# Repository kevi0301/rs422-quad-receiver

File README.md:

# RS-422 Quad Receiver PCB

4-channel RS-422 receiver PCB designed in KiCad with AC termination, TVS protection, test points, and fabrication outputs. 
## Features
- 4-channel RS-422 differential receiver
- AM26C32 receiver IC
- SM712 TVS protection for each input channel
- Configurable enable control with pull-up and pull-down resistors
- Power indicator with LED and 5V power input
- Local 0.1 uF decoupling capacitor
- Test points included in 5V, GND, and Y1-Y4 outputs
- 2-layer PCB with ground copper plane
- Mounting holes with copper keep-out areas
## PCB Design
- Designed and routed in KiCad
- Top and bottom copper routing
- Ground plane implemented on B.Cu
- DRC completed with 0 violations and 0 unrouted connections
- Silkscreen labeling added for debugging and board identification
## Fabrication
Gerber and Excellon PTH/NPTH drill files are included in the Fabrication folder.
## Project Status
PCB design and fabrication files complete. Physical fabrication and hardware validation have not yet been performed.

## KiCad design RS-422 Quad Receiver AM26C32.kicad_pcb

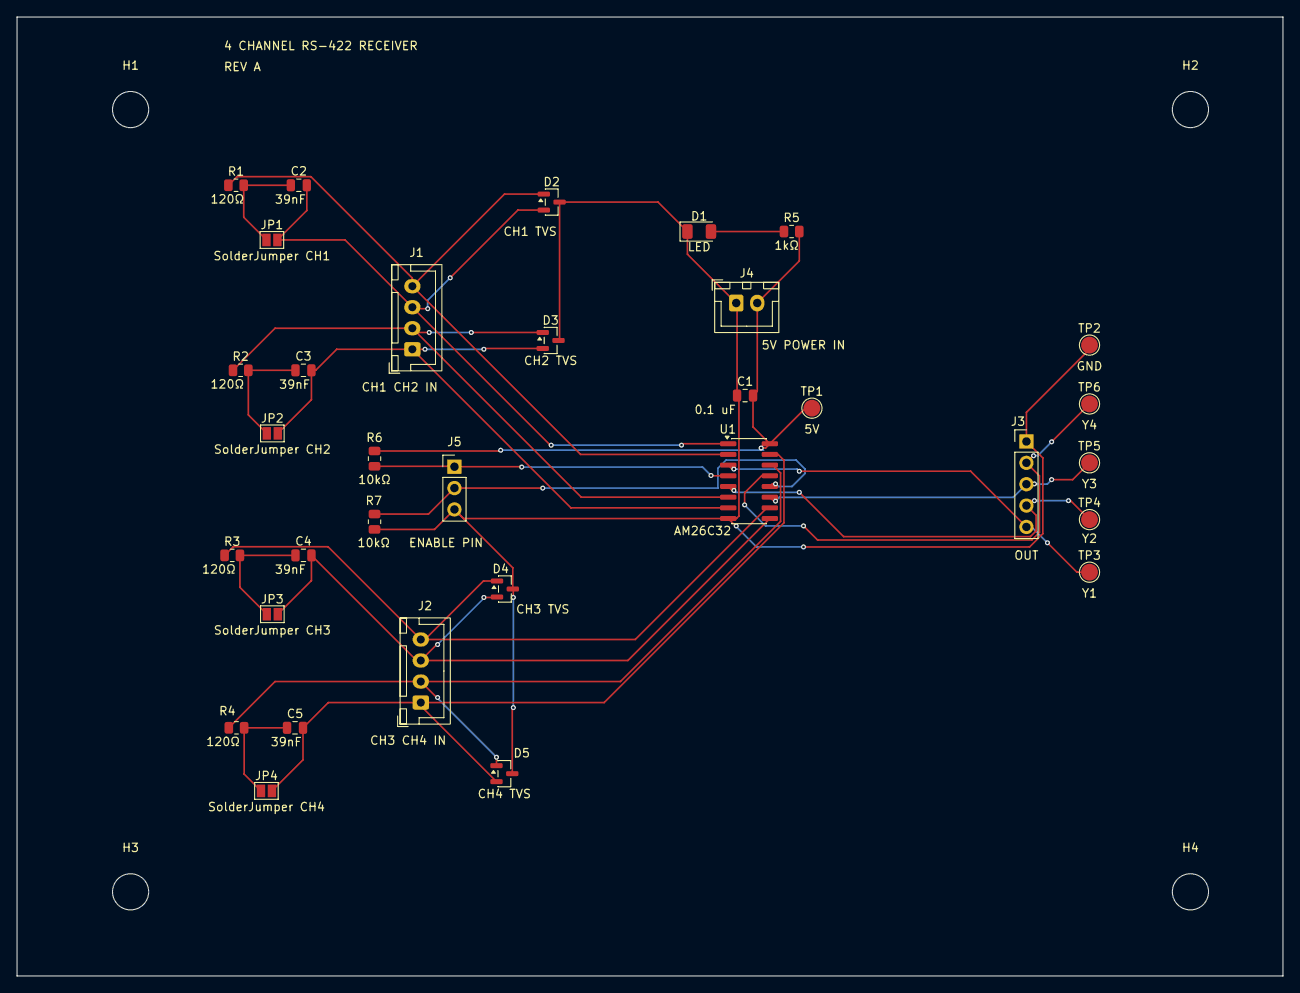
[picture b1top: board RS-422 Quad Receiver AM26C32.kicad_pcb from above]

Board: 2 copper layers, 150.5 x 114.0 mm, 37 parts (0 on the bottom side), 21 nets.

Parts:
C1: 0.1 uF; C_0805_2012Metric
C2, C3, C4, C5: 39nF; C_0805_2012Metric
D1: LED; LED_1206_3216Metric
D2: CH1 TVS; SOT-23
D3: CH2 TVS; SOT-23
D4: CH3 TVS; SOT-23
D5: CH4 TVS; SOT-23
H1, H2, H3, H4: MountingHole; MountingHole_4.3mm_M4
J1: CH1 CH2 IN; JST_XH_B4B-XH-A_1x04_P2.50mm_Vertical
J2: CH3 CH4 IN; JST_XH_B4B-XH-A_1x04_P2.50mm_Vertical
J3: OUT; PinHeader_1x05_P2.54mm_Vertical
J4: 5V POWER IN; JST_XH_B2B-XH-A_1x02_P2.50mm_Vertical
J5: ENABLE PIN; PinHeader_1x03_P2.54mm_Vertical
JP1: SolderJumper CH1; SolderJumper-2_P1.3mm_Open_Pad1.0x1.5mm
JP2: SolderJumper CH2; SolderJumper-2_P1.3mm_Open_Pad1.0x1.5mm
JP3: SolderJumper CH3; SolderJumper-2_P1.3mm_Open_Pad1.0x1.5mm
JP4: SolderJumper CH4; SolderJumper-2_P1.3mm_Open_Pad1.0x1.5mm
R1, R2, R3, R4: 120Ω; R_0805_2012Metric
R5: 1kΩ; R_0805_2012Metric
R6, R7: 10kΩ; R_0805_2012Metric
TP1: 5V; TestPoint_Pad_D2.0mm
TP2: GND; TestPoint_Pad_D2.0mm
TP3: Y1; TestPoint_Pad_D2.0mm
TP4: Y2; TestPoint_Pad_D2.0mm
TP5: Y3; TestPoint_Pad_D2.0mm
TP6: Y4; TestPoint_Pad_D2.0mm
U1: AM26C32; SOIC-16_3.9x9.9mm_P1.27mm

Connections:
+5V: C1.2, J4.2, R5.2, R6.1, TP1.1 (1_1), U1.16 (VDD)
/1A: D2.1 (A1), J1.4, R1.1, U1.2 (1A)
/1B: C2.2, D2.2 (A2), J1.3, JP1.2 (B), U1.1 (1B)
/2A: D3.1 (A1), J1.2, R2.1, U1.6 (2A)
/2B: C3.2, D3.2 (A2), J1.1, JP2.2 (B), U1.7 (2B)
/3A: D4.1 (A1), J2.4, R3.1, U1.10 (3A)
/3B: C4.2, D4.2 (A2), J2.3, JP3.2 (B), U1.9 (3B)
/4A: D5.1 (A1), J2.2, R4.1, U1.14 (4A)
/4B: C5.2, D5.2 (A2), J2.1, JP4.2 (B), U1.15 (4B)
/G: J5.1, R6.2, U1.4 (G)
/Y1: J3.5, TP3.1 (1_1), U1.3 (1Y)
/Y2: J3.4, TP4.1 (1_1), U1.5 (2Y)
/Y3: J3.3, TP5.1 (1_1), U1.11 (3Y)
/Y4: J3.2, TP6.1 (1_1), U1.13 (4Y)
/Ḡ: J5.2, R7.1, U1.12 (~G)
GND: C1.1, D1.1 (K), D2.3 (common), D3.3 (common), D4.3 (common), D5.3 (common), J3.1, J4.1, J5.3, R7.2, TP2.1 (1_1), U1.8 (GND)
unnamed: D1.2 (A), R5.1
unnamed: C2.1, JP1.1 (A), R1.2
unnamed: C3.1, JP2.1 (A), R2.2
unnamed: C4.1, JP3.1 (A), R3.2
unnamed: C5.1, JP4.1 (A), R4.2
